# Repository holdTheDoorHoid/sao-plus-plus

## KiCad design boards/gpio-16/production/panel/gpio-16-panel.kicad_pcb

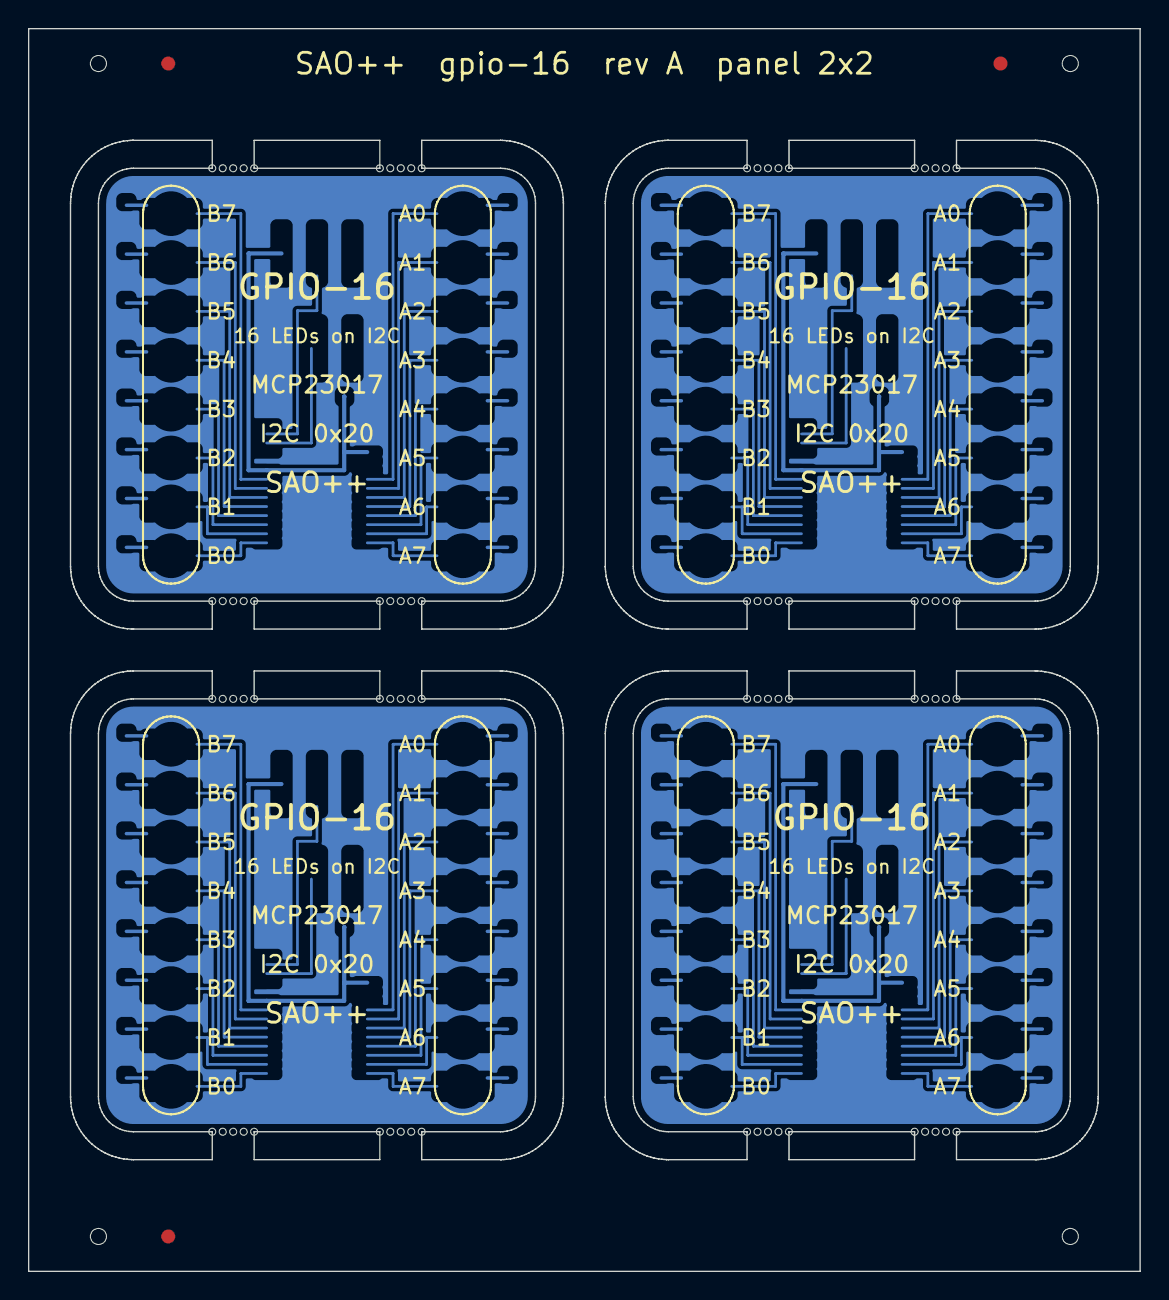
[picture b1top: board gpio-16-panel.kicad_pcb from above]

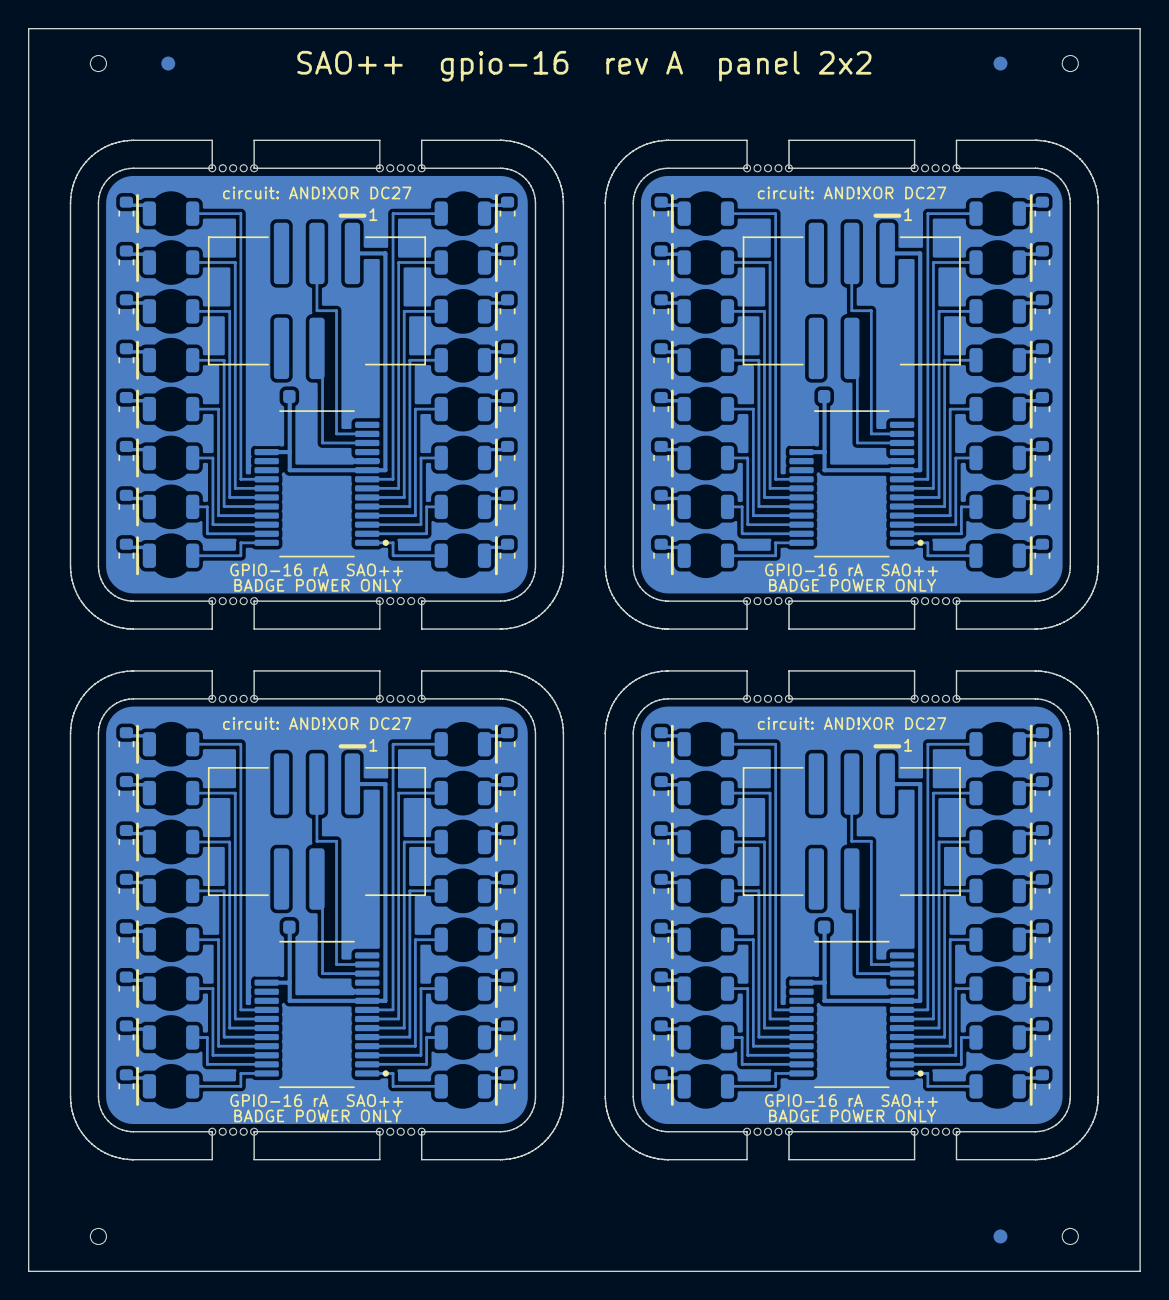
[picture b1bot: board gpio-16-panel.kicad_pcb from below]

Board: 2 copper layers, 79.6 x 89.0 mm, 140 parts (140 on the bottom side), 144 nets.

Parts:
C101, C201, C301, C401: 100n; SAOPP_C_0603_1608Metric
D101, D102, D103, D104, D105, D106, D107, D108, D109, D110, D111, D112, D113, D114, D115, D116, D201, D202, D203, D204, D205, D206, D207, D208, D209, D210, D211, D212, D213, D214, D215, D216, D301, D302, D303, D304, D305, D306, D307, D308, D309, D310, D311, D312, D313, D314, D315, D316, D401, D402, D403, D404, D405, D406, D407, D408, D409, D410, D411, D412, D413, D414, D415, D416: red; SAOPP_LED-10_1206_ReverseMount_ThroughBoard
J101, J201, J301, J401: SAO v1.69bis; SAOPP_CONN-01_BoxHeader_2x03_P2.54mm_SMD_XFCN_BH254VS-6P
R101, R102, R103, R104, R105, R106, R107, R108, R109, R110, R111, R112, R113, R114, R115, R116, R201, R202, R203, R204, R205, R206, R207, R208, R209, R210, R211, R212, R213, R214, R215, R216, R301, R302, R303, R304, R305, R306, R307, R308, R309, R310, R311, R312, R313, R314, R315, R316, R401, R402, R403, R404, R405, R406, R407, R408, R409, R410, R411, R412, R413, R414, R415, R416: 1.3k; SAOPP_R_0603_1608Metric
U101, U201, U301, U401: MCP23017; SSOP-28_5.3x10.2mm_P0.65mm_Microchip_C04-2073A

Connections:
B2-D1_K: D201.1, R201.1
B2-D2_K: D202.1, R202.1
B2-D3_K: D203.1, R203.1
B2-D4_K: D204.1, R204.1
B2-D5_K: D205.1, R205.1
B2-D6_K: D206.1, R206.1
B2-D7_K: D207.1, R207.1
B2-D8_K: D208.1, R208.1
B2-D9_K: D209.1, R209.1
B2-D10_K: D210.1, R210.1
B2-D11_K: D211.1, R211.1
B2-D12_K: D212.1, R212.1
B2-D13_K: D213.1, R213.1
B2-D14_K: D214.1, R214.1
B2-D15_K: D215.1, R215.1
B2-D16_K: D216.1, R216.1
B2-GND: C201.2, J201.2, R201.2, R202.2, R203.2, R204.2, R205.2, R206.2, R207.2, R208.2, R209.2, R210.2, R211.2, R212.2, R213.2, R214.2, R215.2, R216.2, U201.10, U201.15, U201.16, U201.17
B2-GPA0: D201.2, U201.21
B2-GPA1: D202.2, U201.22
B2-GPA2: D203.2, U201.23
B2-GPA3: D204.2, U201.24
B2-GPA4: D205.2, U201.25
B2-GPA5: D206.2, U201.26
B2-GPA6: D207.2, U201.27
B2-GPA7: D208.2, U201.28
B2-GPB0: D209.2, U201.1
B2-GPB1: D210.2, U201.2
B2-GPB2: D211.2, U201.3
B2-GPB3: D212.2, U201.4
B2-GPB4: D213.2, U201.5
B2-GPB5: D214.2, U201.6
B2-GPB6: D215.2, U201.7
B2-GPB7: D216.2, U201.8
B2-SCL: J201.4, U201.12
B2-SDA: J201.3, U201.13
B2-VSAO: C201.1, J201.1, U201.9, U201.18
B3-D1_K: D301.1, R301.1
B3-D2_K: D302.1, R302.1
B3-D3_K: D303.1, R303.1
B3-D4_K: D304.1, R304.1
B3-D5_K: D305.1, R305.1
B3-D6_K: D306.1, R306.1
B3-D7_K: D307.1, R307.1
B3-D8_K: D308.1, R308.1
B3-D9_K: D309.1, R309.1
B3-D10_K: D310.1, R310.1
B3-D11_K: D311.1, R311.1
B3-D12_K: D312.1, R312.1
B3-D13_K: D313.1, R313.1
B3-D14_K: D314.1, R314.1
B3-D15_K: D315.1, R315.1
B3-D16_K: D316.1, R316.1
B3-GND: C301.2, J301.2, R301.2, R302.2, R303.2, R304.2, R305.2, R306.2, R307.2, R308.2, R309.2, R310.2, R311.2, R312.2, R313.2, R314.2, R315.2, R316.2, U301.10, U301.15, U301.16, U301.17
B3-GPA0: D301.2, U301.21
B3-GPA1: D302.2, U301.22
B3-GPA2: D303.2, U301.23
B3-GPA3: D304.2, U301.24
B3-GPA4: D305.2, U301.25
B3-GPA5: D306.2, U301.26
B3-GPA6: D307.2, U301.27
B3-GPA7: D308.2, U301.28
B3-GPB0: D309.2, U301.1
B3-GPB1: D310.2, U301.2
B3-GPB2: D311.2, U301.3
B3-GPB3: D312.2, U301.4
B3-GPB4: D313.2, U301.5
B3-GPB5: D314.2, U301.6
B3-GPB6: D315.2, U301.7
B3-GPB7: D316.2, U301.8
B3-SCL: J301.4, U301.12
B3-SDA: J301.3, U301.13
B3-VSAO: C301.1, J301.1, U301.9, U301.18
B4-D1_K: D401.1, R401.1
B4-D2_K: D402.1, R402.1
B4-D3_K: D403.1, R403.1
B4-D4_K: D404.1, R404.1
B4-D5_K: D405.1, R405.1
B4-D6_K: D406.1, R406.1
B4-D7_K: D407.1, R407.1
B4-D8_K: D408.1, R408.1
B4-D9_K: D409.1, R409.1
B4-D10_K: D410.1, R410.1
B4-D11_K: D411.1, R411.1
B4-D12_K: D412.1, R412.1
B4-D13_K: D413.1, R413.1
B4-D14_K: D414.1, R414.1
B4-D15_K: D415.1, R415.1
B4-D16_K: D416.1, R416.1
B4-GND: C401.2, J401.2, R401.2, R402.2, R403.2, R404.2, R405.2, R406.2, R407.2, R408.2, R409.2, R410.2, R411.2, R412.2, R413.2, R414.2, R415.2, R416.2, U401.10, U401.15, U401.16, U401.17
B4-GPA0: D401.2, U401.21
B4-GPA1: D402.2, U401.22
B4-GPA2: D403.2, U401.23
B4-GPA3: D404.2, U401.24
B4-GPA4: D405.2, U401.25
B4-GPA5: D406.2, U401.26
B4-GPA6: D407.2, U401.27
B4-GPA7: D408.2, U401.28
B4-GPB0: D409.2, U401.1
B4-GPB1: D410.2, U401.2
B4-GPB2: D411.2, U401.3
B4-GPB3: D412.2, U401.4
B4-GPB4: D413.2, U401.5
B4-GPB5: D414.2, U401.6
B4-GPB6: D415.2, U401.7
B4-GPB7: D416.2, U401.8
B4-SCL: J401.4, U401.12
B4-SDA: J401.3, U401.13
B4-VSAO: C401.1, J401.1, U401.9, U401.18
D1_K: D101.1, R101.1
D2_K: D102.1, R102.1
D3_K: D103.1, R103.1
D4_K: D104.1, R104.1
D5_K: D105.1, R105.1
D6_K: D106.1, R106.1
D7_K: D107.1, R107.1
D8_K: D108.1, R108.1
D9_K: D109.1, R109.1
D10_K: D110.1, R110.1
D11_K: D111.1, R111.1
D12_K: D112.1, R112.1
D13_K: D113.1, R113.1
D14_K: D114.1, R114.1
D15_K: D115.1, R115.1
D16_K: D116.1, R116.1
GND: C101.2, J101.2, R101.2, R102.2, R103.2, R104.2, R105.2, R106.2, R107.2, R108.2, R109.2, R110.2, R111.2, R112.2, R113.2, R114.2, R115.2, R116.2, U101.10, U101.15, U101.16, U101.17
GPA0: D101.2, U101.21
GPA1: D102.2, U101.22
GPA2: D103.2, U101.23
GPA3: D104.2, U101.24
GPA4: D105.2, U101.25
GPA5: D106.2, U101.26
GPA6: D107.2, U101.27
GPA7: D108.2, U101.28
GPB0: D109.2, U101.1
GPB1: D110.2, U101.2
GPB2: D111.2, U101.3
GPB3: D112.2, U101.4
GPB4: D113.2, U101.5
GPB5: D114.2, U101.6
GPB6: D115.2, U101.7
GPB7: D116.2, U101.8
SCL: J101.4, U101.12
SDA: J101.3, U101.13
VSAO: C101.1, J101.1, U101.9, U101.18

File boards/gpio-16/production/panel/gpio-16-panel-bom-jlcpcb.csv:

Comment,Designator,Footprint,LCSC Part #
100n,"C101,C201,C301,C401",SAOPP_C_0603_1608Metric,C14663
red,"D101,D102,D103,D104,D105,D106,D107,D108,D109,D110,D111,D112,D113,D114,D115,D116,D201,D202,D203,D204,D205,D206,D207,D208,D209,D210,D211,D212,D213,D214,D215,D216,D301,D302,D303,D304,D305,D306,D307,D308,D309,D310,D311,D312,D313,D314,D315,D316,D401,D402,D403,D404,D405,D406,D407,D408,D409,D410,D411,D412,D413,D414,D415,D416",SAOPP_LED-10_1206_ReverseMount_ThroughBoard,C125107
SAO v1.69bis,"J101,J201,J301,J401",SAOPP_CONN-01_BoxHeader_2x03_P2.54mm_SMD_XFCN_BH254VS-6P,C492445
1.3k,"R101,R102,R103,R104,R105,R106,R107,R108,R109,R110,R111,R112,R113,R114,R115,R116,R201,R202,R203,R204,R205,R206,R207,R208,R209,R210,R211,R212,R213,R214,R215,R216,R301,R302,R303,R304,R305,R306,R307,R308,R309,R310,R311,R312,R313,R314,R315,R316,R401,R402,R403,R404,R405,R406,R407,R408,R409,R410,R411,R412,R413,R414,R415,R416",SAOPP_R_0603_1608Metric,C22767
MCP23017,"U101,U201,U301,U401",SSOP-28_5.3x10.2mm_P0.65mm_Microchip_C04-2073A,C558584

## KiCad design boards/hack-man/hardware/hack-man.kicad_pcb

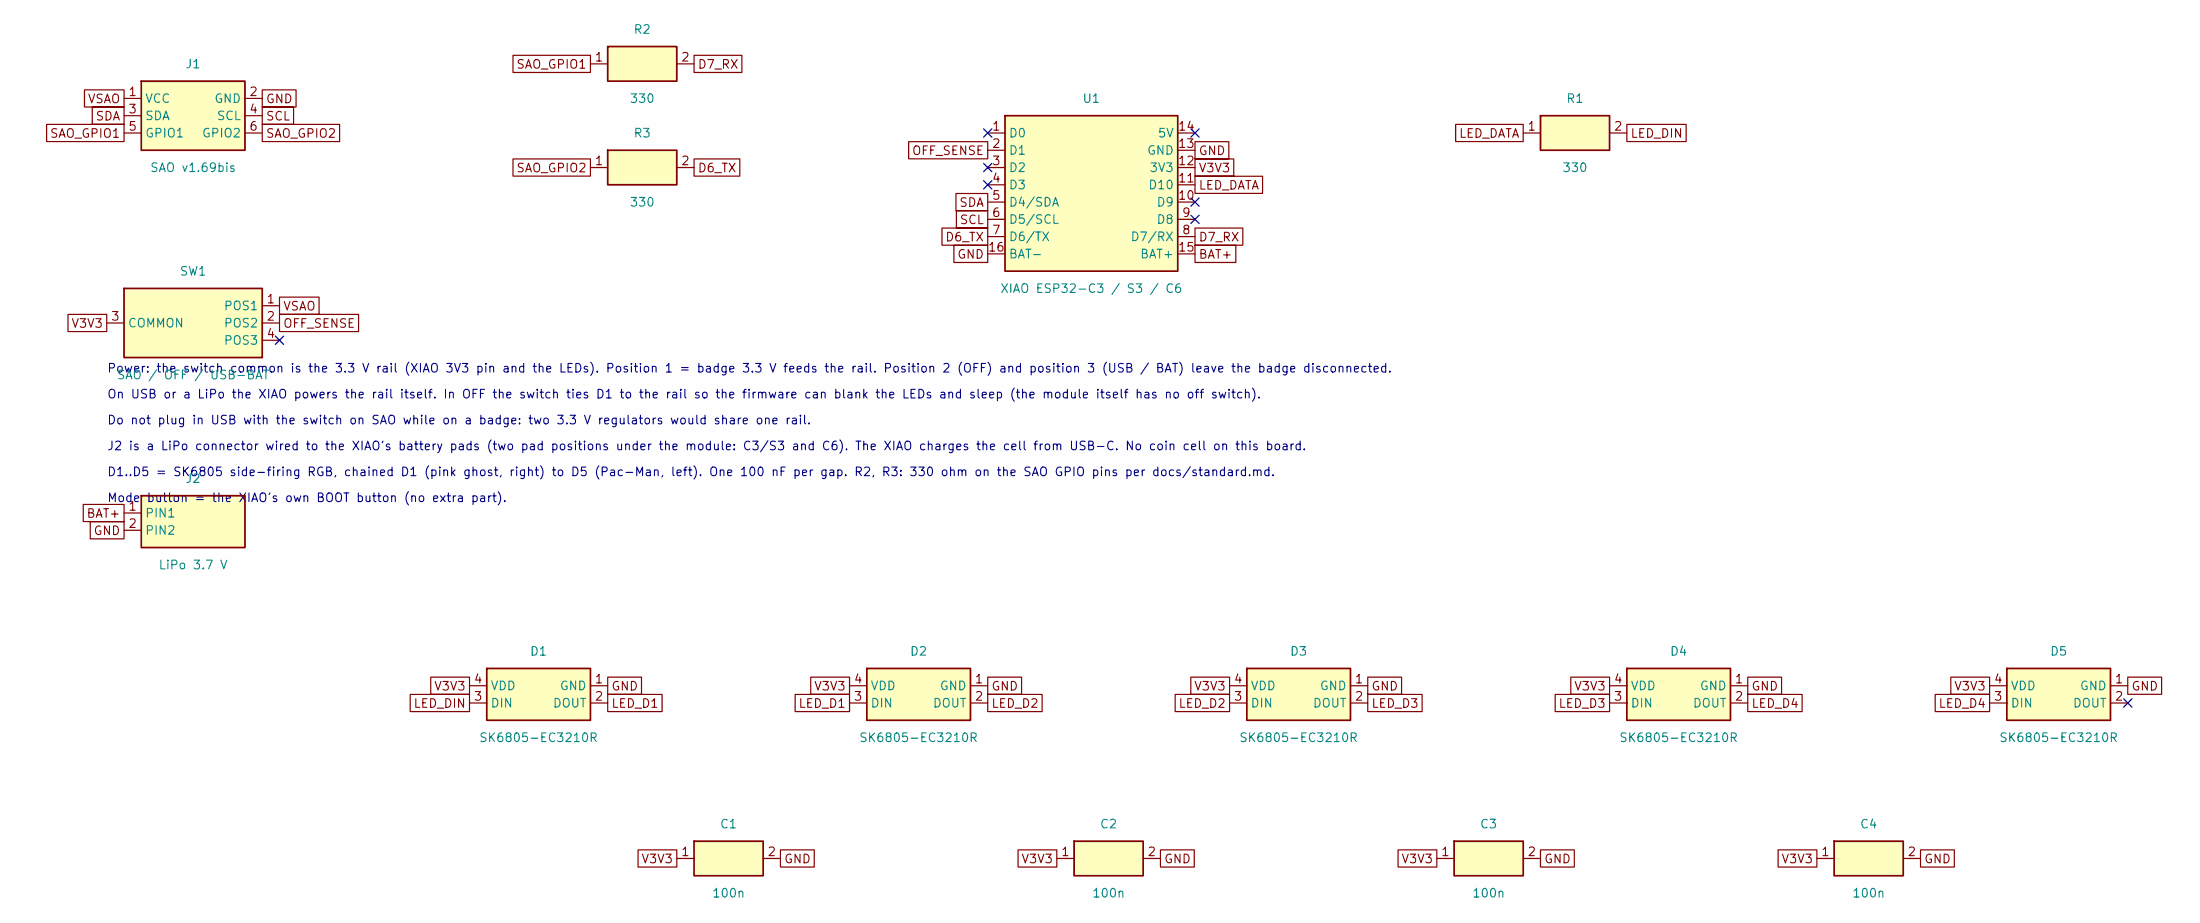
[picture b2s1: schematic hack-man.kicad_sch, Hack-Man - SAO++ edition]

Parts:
C1, C2, C3, C4: 100n; SAOPP_C_0603_1608Metric; MPN CC0603KRX7R9BB104; LCSC C14663
D1, D2, D3, D4, D5: SK6805-EC3210R; SAOPP_LED-20_SK6805-EC3210R_SideView_RGB; MPN SK6805-EC3210R; LCSC C5378735
J1: SAO v1.69bis; SAOPP_CONN-01_BoxHeader_2x03_P2.54mm_SMD_XFCN_BH254VS-6P; MPN BH254VS-6P; LCSC C492445
J2: LiPo 3.7 V; SAOPP_CONN-10_JST_PH_S2B-PH-SM4-TB_1x02_Horizontal; MPN S2B-PH-SM4-TB(LF)(SN); LCSC C295747
R1, R2, R3: 330; SAOPP_R_0603_1608Metric; MPN 0603WAF3300T5E; LCSC C23138
SW1: SAO / OFF / USB-BAT; SAOPP_SW-01_Slide_SP3T_CK_PCM13SMTR; MPN PCM13SMTR; LCSC C221842
U1: XIAO ESP32-C3 / S3 / C6; SAOPP_MCU-01_Seeed_XIAO_SMD_C3_S3_C6; MPN XIAO ESP32-C3 / S3 / C6

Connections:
BAT+: J2.1 (PIN1), U1.15 (BAT+)
D6_TX: R3.2, U1.7 (D6/TX)
D7_RX: R2.2, U1.8 (D7/RX)
GND: C1.2, C2.2, C3.2, C4.2, D1.1 (GND), D2.1 (GND), D3.1 (GND), D4.1 (GND), D5.1 (GND), J1.2 (GND), J2.2 (PIN2), U1.13 (GND), U1.16 (BAT-)
LED_D1: D1.2 (DOUT), D2.3 (DIN)
LED_D2: D2.2 (DOUT), D3.3 (DIN)
LED_D3: D3.2 (DOUT), D4.3 (DIN)
LED_D4: D4.2 (DOUT), D5.3 (DIN)
LED_DATA: R1.1, U1.11 (D10)
LED_DIN: D1.3 (DIN), R1.2
OFF_SENSE: SW1.2 (POS2), U1.2 (D1)
SAO_GPIO1: J1.5 (GPIO1), R2.1
SAO_GPIO2: J1.6 (GPIO2), R3.1
SCL: J1.4 (SCL), U1.6 (D5/SCL)
SDA: J1.3 (SDA), U1.5 (D4/SDA)
V3V3: C1.1, C2.1, C3.1, C4.1, D1.4 (VDD), D2.4 (VDD), D3.4 (VDD), D4.4 (VDD), D5.4 (VDD), SW1.3 (COMMON), U1.12 (3V3)
VSAO: J1.1 (VCC), SW1.1 (POS1)

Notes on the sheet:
Power: the switch common is the 3.3 V rail (XIAO 3V3 pin and the LEDs). Position 1 = badge 3.3 V feeds the rail. Position 2 (OFF) and position 3 (USB / BAT) leave the badge disconnected.
On USB or a LiPo the XIAO powers the rail itself. In OFF the switch ties D1 to the rail so the firmware can blank the LEDs and sleep (the module itself has no off switch).
Do not plug in USB with the switch on SAO while on a badge: two 3.3 V regulators would share one rail.
J2 is a LiPo connector wired to the XIAO's battery pads (two pad positions under the module: C3/S3 and C6). The XIAO charges the cell from USB-C. No coin cell on this board.
D1..D5 = SK6805 side-firing RGB, chained D1 (pink ghost, right) to D5 (Pac-Man, left). One 100 nF per gap. R2, R3: 330 ohm on the SAO GPIO pins per docs/standard.md.
Mode button = the XIAO's own BOOT button (no extra part).

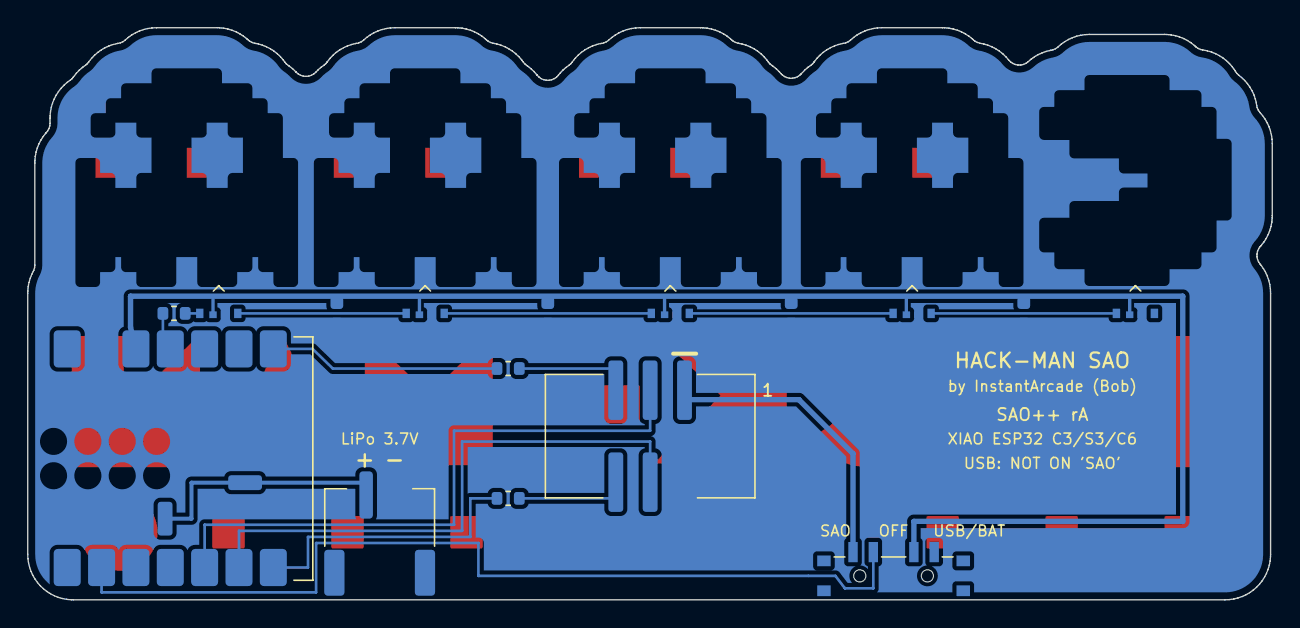
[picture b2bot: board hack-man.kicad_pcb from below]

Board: 2 copper layers, 92.0 x 42.3 mm, 16 parts (16 on the bottom side), 17 nets.

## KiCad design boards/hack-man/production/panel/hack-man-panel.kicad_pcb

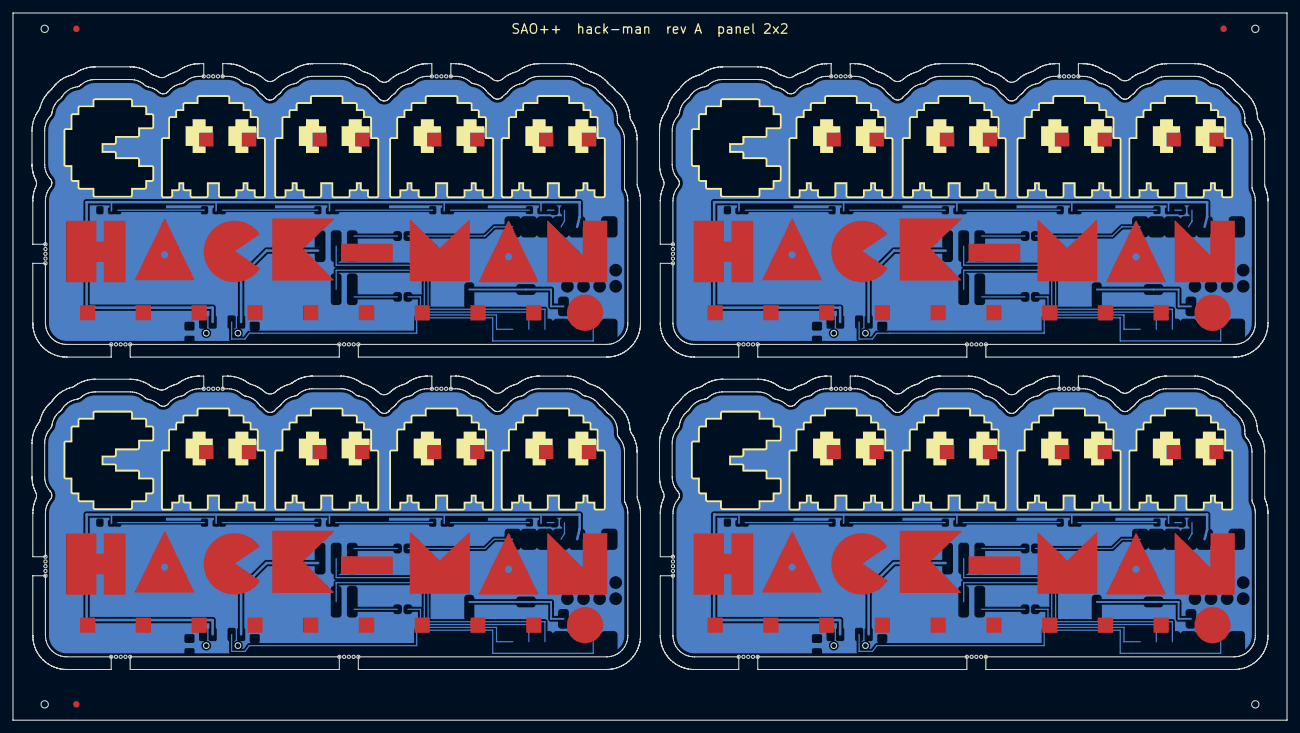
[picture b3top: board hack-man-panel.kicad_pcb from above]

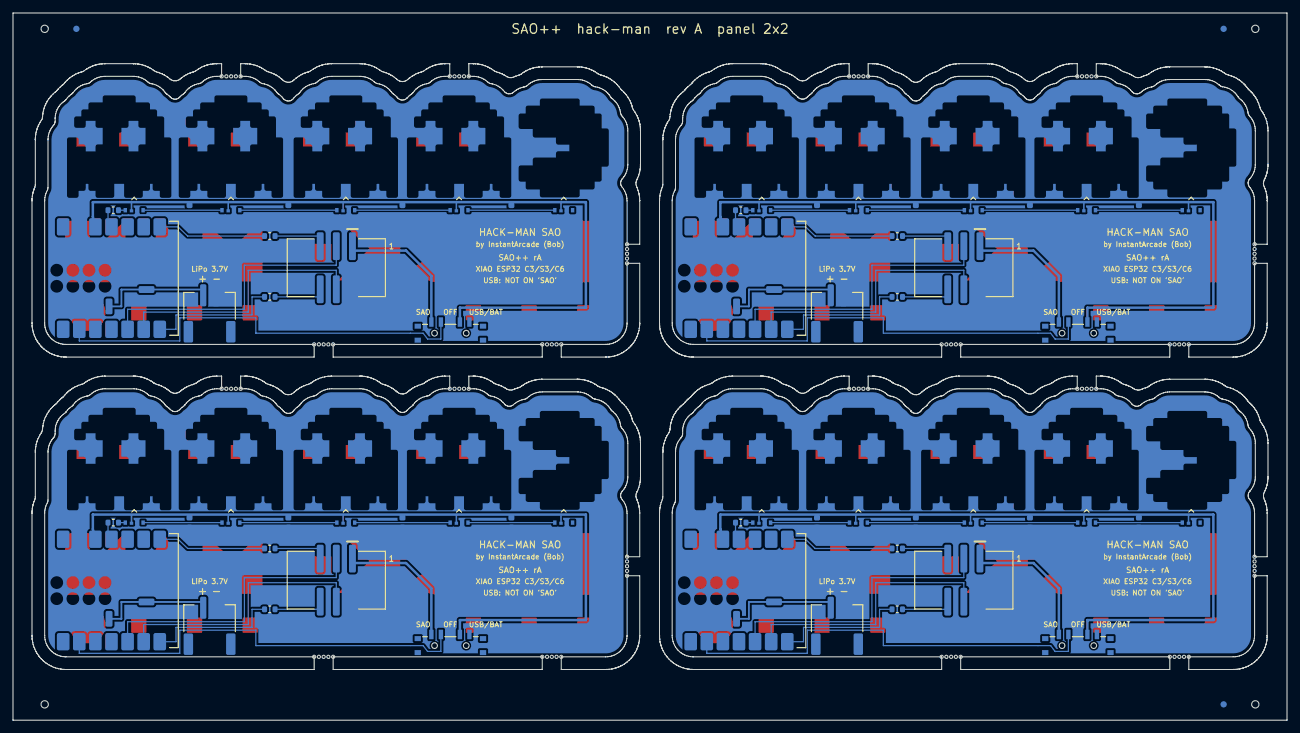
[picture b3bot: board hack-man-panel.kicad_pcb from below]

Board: 2 copper layers, 201.0 x 111.6 mm, 64 parts (64 on the bottom side), 68 nets.

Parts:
C101, C102, C103, C104, C201, C202, C203, C204, C301, C302, C303, C304, C401, C402, C403, C404: 100n; SAOPP_C_0603_1608Metric
D101, D102, D103, D104, D105, D201, D202, D203, D204, D205, D301, D302, D303, D304, D305, D401, D402, D403, D404, D405: SK6805-EC3210R; SAOPP_LED-20_SK6805-EC3210R_SideView_RGB
J101, J201, J301, J401: SAO v1.69bis; SAOPP_CONN-01_BoxHeader_2x03_P2.54mm_SMD_XFCN_BH254VS-6P
J102, J202, J302, J402: LiPo 3.7 V; SAOPP_CONN-10_JST_PH_S2B-PH-SM4-TB_1x02_Horizontal
R101, R102, R103, R201, R202, R203, R301, R302, R303, R401, R402, R403: 330; SAOPP_R_0603_1608Metric
SW101, SW201, SW301, SW401: SAO / OFF / USB-BAT; SAOPP_SW-01_Slide_SP3T_CK_PCM13SMTR
U101, U201, U301, U401: XIAO ESP32-C3 / S3 / C6; SAOPP_MCU-01_Seeed_XIAO_SMD_C3_S3_C6

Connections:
B2-BAT+: J202.1, U201.15
B2-D6_TX: R203.2, U201.7
B2-D7_RX: R202.2, U201.8
B2-GND: C201.2, C202.2, C203.2, C204.2, D201.1, D202.1, D203.1, D204.1, D205.1, J201.2, J202.2, U201.13, U201.16
B2-LED_D1: D201.2, D202.3
B2-LED_D2: D202.2, D203.3
B2-LED_D3: D203.2, D204.3
B2-LED_D4: D204.2, D205.3
B2-LED_DATA: R201.1, U201.11
B2-LED_DIN: D201.3, R201.2
B2-OFF_SENSE: SW201.2, U201.2
B2-SAO_GPIO1: J201.5, R202.1
B2-SAO_GPIO2: J201.6, R203.1
B2-SCL: J201.4, U201.6
B2-SDA: J201.3, U201.5
B2-V3V3: C201.1, C202.1, C203.1, C204.1, D201.4, D202.4, D203.4, D204.4, D205.4, SW201.3, U201.12
B2-VSAO: J201.1, SW201.1
B3-BAT+: J302.1, U301.15
B3-D6_TX: R303.2, U301.7
B3-D7_RX: R302.2, U301.8
B3-GND: C301.2, C302.2, C303.2, C304.2, D301.1, D302.1, D303.1, D304.1, D305.1, J301.2, J302.2, U301.13, U301.16
B3-LED_D1: D301.2, D302.3
B3-LED_D2: D302.2, D303.3
B3-LED_D3: D303.2, D304.3
B3-LED_D4: D304.2, D305.3
B3-LED_DATA: R301.1, U301.11
B3-LED_DIN: D301.3, R301.2
B3-OFF_SENSE: SW301.2, U301.2
B3-SAO_GPIO1: J301.5, R302.1
B3-SAO_GPIO2: J301.6, R303.1
B3-SCL: J301.4, U301.6
B3-SDA: J301.3, U301.5
B3-V3V3: C301.1, C302.1, C303.1, C304.1, D301.4, D302.4, D303.4, D304.4, D305.4, SW301.3, U301.12
B3-VSAO: J301.1, SW301.1
B4-BAT+: J402.1, U401.15
B4-D6_TX: R403.2, U401.7
B4-D7_RX: R402.2, U401.8
B4-GND: C401.2, C402.2, C403.2, C404.2, D401.1, D402.1, D403.1, D404.1, D405.1, J401.2, J402.2, U401.13, U401.16
B4-LED_D1: D401.2, D402.3
B4-LED_D2: D402.2, D403.3
B4-LED_D3: D403.2, D404.3
B4-LED_D4: D404.2, D405.3
B4-LED_DATA: R401.1, U401.11
B4-LED_DIN: D401.3, R401.2
B4-OFF_SENSE: SW401.2, U401.2
B4-SAO_GPIO1: J401.5, R402.1
B4-SAO_GPIO2: J401.6, R403.1
B4-SCL: J401.4, U401.6
B4-SDA: J401.3, U401.5
B4-V3V3: C401.1, C402.1, C403.1, C404.1, D401.4, D402.4, D403.4, D404.4, D405.4, SW401.3, U401.12
B4-VSAO: J401.1, SW401.1
BAT+: J102.1, U101.15
D6_TX: R103.2, U101.7
D7_RX: R102.2, U101.8
GND: C101.2, C102.2, C103.2, C104.2, D101.1, D102.1, D103.1, D104.1, D105.1, J101.2, J102.2, U101.13, U101.16
LED_D1: D101.2, D102.3
LED_D2: D102.2, D103.3
LED_D3: D103.2, D104.3
LED_D4: D104.2, D105.3
LED_DATA: R101.1, U101.11
LED_DIN: D101.3, R101.2
OFF_SENSE: SW101.2, U101.2
SAO_GPIO1: J101.5, R102.1
SAO_GPIO2: J101.6, R103.1
SCL: J101.4, U101.6
SDA: J101.3, U101.5
V3V3: C101.1, C102.1, C103.1, C104.1, D101.4, D102.4, D103.4, D104.4, D105.4, SW101.3, U101.12
VSAO: J101.1, SW101.1

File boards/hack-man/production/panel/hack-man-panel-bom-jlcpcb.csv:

Comment,Designator,Footprint,LCSC Part #
100n,"C101,C102,C103,C104,C201,C202,C203,C204,C301,C302,C303,C304,C401,C402,C403,C404",SAOPP_C_0603_1608Metric,C14663
SK6805-EC3210R,"D101,D102,D103,D104,D105,D201,D202,D203,D204,D205,D301,D302,D303,D304,D305,D401,D402,D403,D404,D405",SAOPP_LED-20_SK6805-EC3210R_SideView_RGB,C5378735
SAO v1.69bis,"J101,J201,J301,J401",SAOPP_CONN-01_BoxHeader_2x03_P2.54mm_SMD_XFCN_BH254VS-6P,C492445
LiPo 3.7 V,"J102,J202,J302,J402",SAOPP_CONN-10_JST_PH_S2B-PH-SM4-TB_1x02_Horizontal,C295747
330,"R101,R102,R103,R201,R202,R203,R301,R302,R303,R401,R402,R403",SAOPP_R_0603_1608Metric,C23138
SAO / OFF / USB-BAT,"SW101,SW201,SW301,SW401",SAOPP_SW-01_Slide_SP3T_CK_PCM13SMTR,C221842
XIAO ESP32-C3 / S3 / C6,"U101,U201,U301,U401",SAOPP_MCU-01_Seeed_XIAO_SMD_C3_S3_C6,

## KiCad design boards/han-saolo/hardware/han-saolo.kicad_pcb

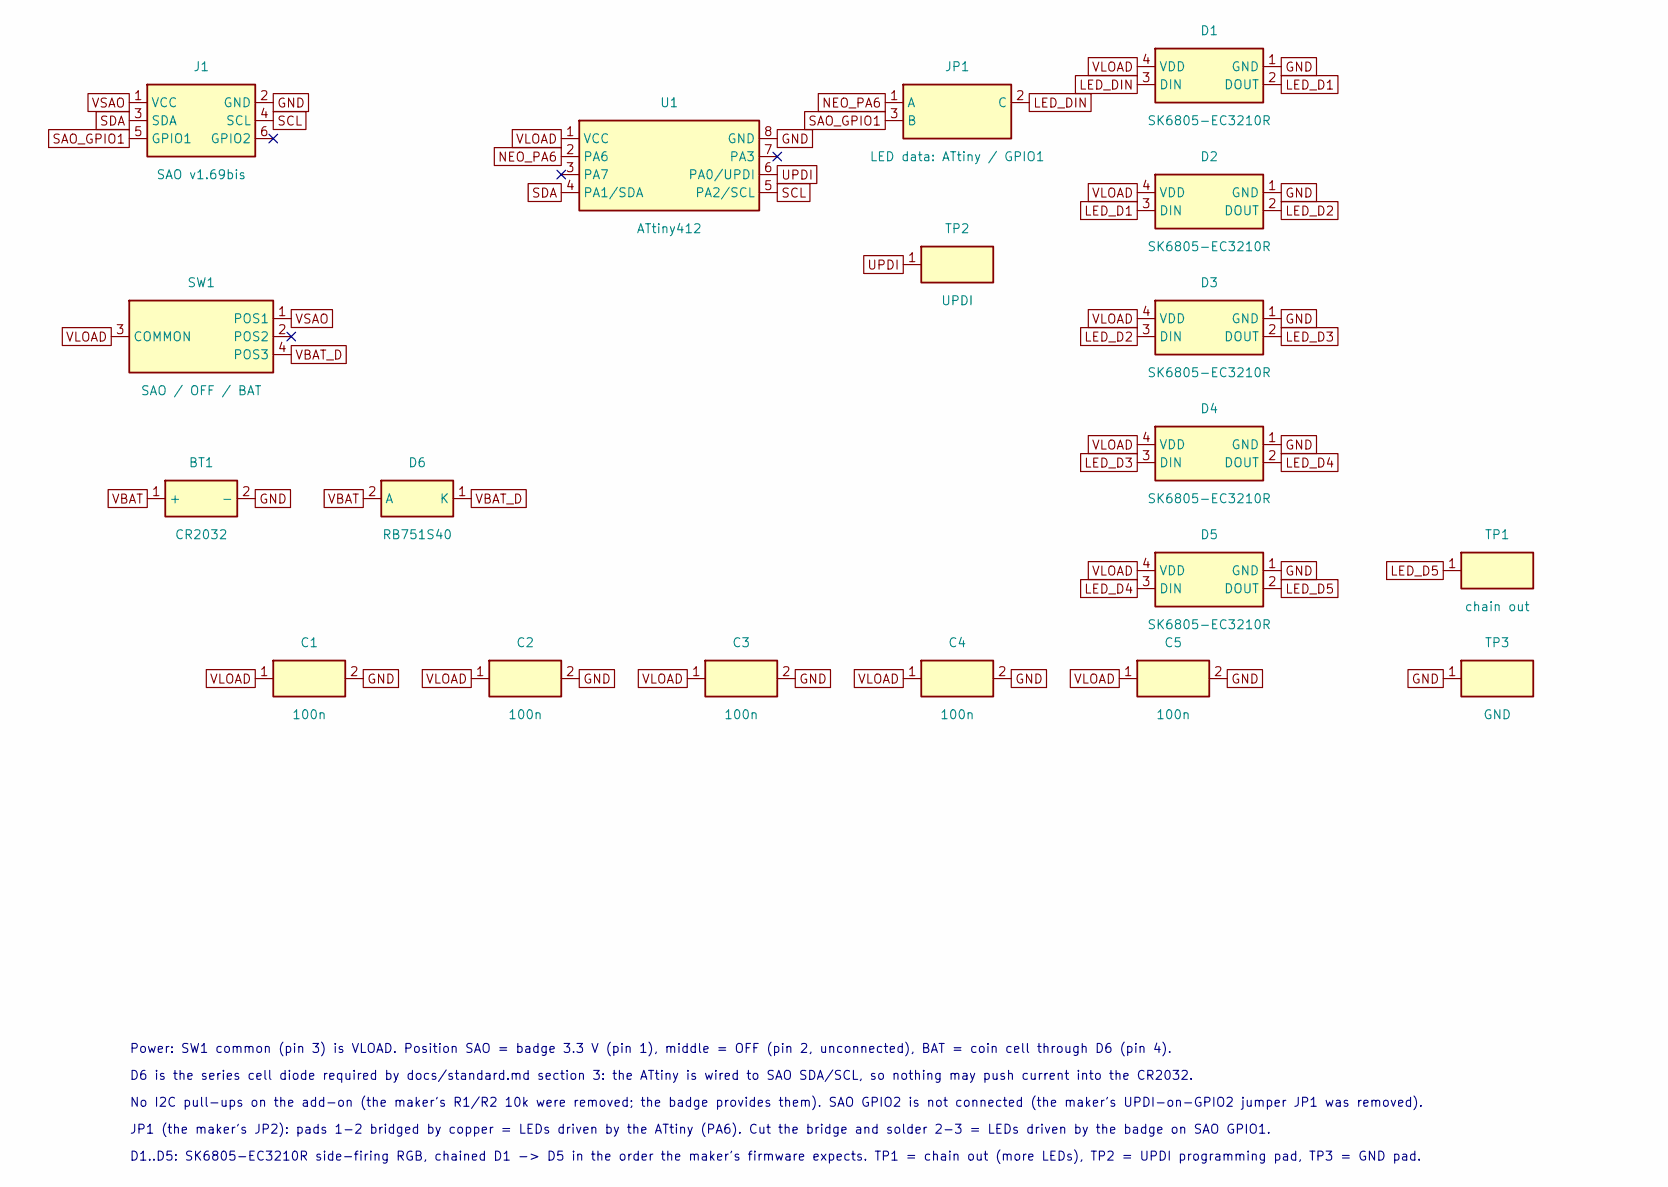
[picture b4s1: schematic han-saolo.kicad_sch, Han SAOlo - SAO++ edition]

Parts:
BT1: CR2032; SAOPP_BAT-01_CR2032_SMD_TE_BAT-HLD-001; MPN BAT-HLD-001; LCSC C7501066
C1, C2, C3, C4, C5: 100n; SAOPP_C_0603_1608Metric; MPN CC0603KRX7R9BB104; LCSC C14663
D1, D2, D3, D4, D5: SK6805-EC3210R; SAOPP_LED-20_SK6805-EC3210R_SideView_RGB; MPN SK6805-EC3210R; LCSC C5378735
D6: RB751S40; D_SOD-523; MPN RB751S40T1G; LCSC C232576
J1: SAO v1.69bis; SAOPP_CONN-01_BoxHeader_2x03_P2.54mm_SMD_XFCN_BH254VS-6P; MPN BH254VS-6P; LCSC C492445
JP1: LED data: ATtiny / GPIO1; SolderJumper-3_P1.3mm_Bridged2Bar12_RoundedPad1.0x1.5mm; MPN none: PCB copper, nothing fitted
SW1: SAO / OFF / BAT; SAOPP_SW-01_Slide_SP3T_CK_PCM13SMTR; MPN PCM13SMTR; LCSC C221842
TP1: chain out; TestPoint_Pad_D2.0mm; MPN none: bare pad, nothing fitted
TP2: UPDI; TestPoint_Pad_D1.5mm; MPN none: bare pad, nothing fitted
TP3: GND; TestPoint_Pad_D3.0mm; MPN none: bare pad, nothing fitted
U1: ATtiny412; SOIC-8_3.9x4.9mm_P1.27mm; MPN ATTINY412-SSNR; LCSC C1337190

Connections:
GND: BT1.2 (-), C1.2, C2.2, C3.2, C4.2, C5.2, D1.1 (GND), D2.1 (GND), D3.1 (GND), D4.1 (GND), D5.1 (GND), J1.2 (GND), TP3.1, U1.8 (GND)
LED_D1: D1.2 (DOUT), D2.3 (DIN)
LED_D2: D2.2 (DOUT), D3.3 (DIN)
LED_D3: D3.2 (DOUT), D4.3 (DIN)
LED_D4: D4.2 (DOUT), D5.3 (DIN)
LED_D5: D5.2 (DOUT), TP1.1
LED_DIN: D1.3 (DIN), JP1.2 (C)
NEO_PA6: JP1.1 (A), U1.2 (PA6)
SAO_GPIO1: J1.5 (GPIO1), JP1.3 (B)
SCL: J1.4 (SCL), U1.5 (PA2/SCL)
SDA: J1.3 (SDA), U1.4 (PA1/SDA)
UPDI: TP2.1, U1.6 (PA0/UPDI)
VBAT: BT1.1 (+), D6.2 (A)
VBAT_D: D6.1 (K), SW1.4 (POS3)
VLOAD: C1.1, C2.1, C3.1, C4.1, C5.1, D1.4 (VDD), D2.4 (VDD), D3.4 (VDD), D4.4 (VDD), D5.4 (VDD), SW1.3 (COMMON), U1.1 (VCC)
VSAO: J1.1 (VCC), SW1.1 (POS1)

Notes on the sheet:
Power: SW1 common (pin 3) is VLOAD. Position SAO = badge 3.3 V (pin 1), middle = OFF (pin 2, unconnected), BAT = coin cell through D6 (pin 4).
D6 is the series cell diode required by docs/standard.md section 3: the ATtiny is wired to SAO SDA/SCL, so nothing may push current into the CR2032.
No I2C pull-ups on the add-on (the maker's R1/R2 10k were removed; the badge provides them). SAO GPIO2 is not connected (the maker's UPDI-on-GPIO2 jumper JP1 was removed).
JP1 (the maker's JP2): pads 1-2 bridged by copper = LEDs driven by the ATtiny (PA6). Cut the bridge and solder 2-3 = LEDs driven by the badge on SAO GPIO1.
D1..D5: SK6805-EC3210R side-firing RGB, chained D1 -> D5 in the order the maker's firmware expects. TP1 = chain out (more LEDs), TP2 = UPDI programming pad, TP3 = GND pad.

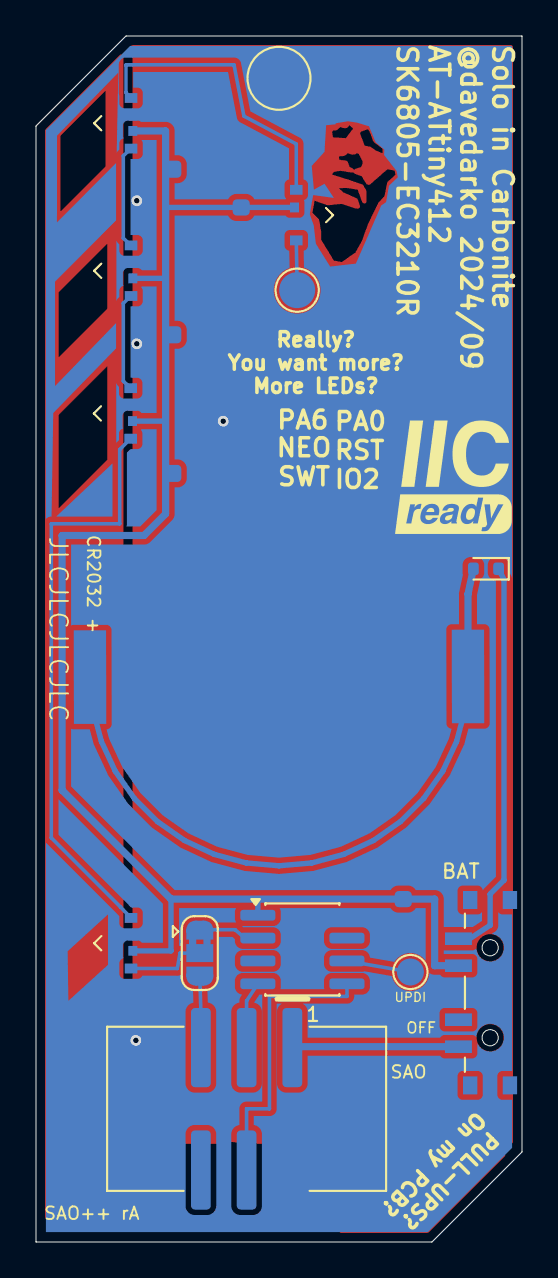
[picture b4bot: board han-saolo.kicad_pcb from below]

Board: 2 copper layers, 27.0 x 67.0 mm, 19 parts (19 on the bottom side), 16 nets.

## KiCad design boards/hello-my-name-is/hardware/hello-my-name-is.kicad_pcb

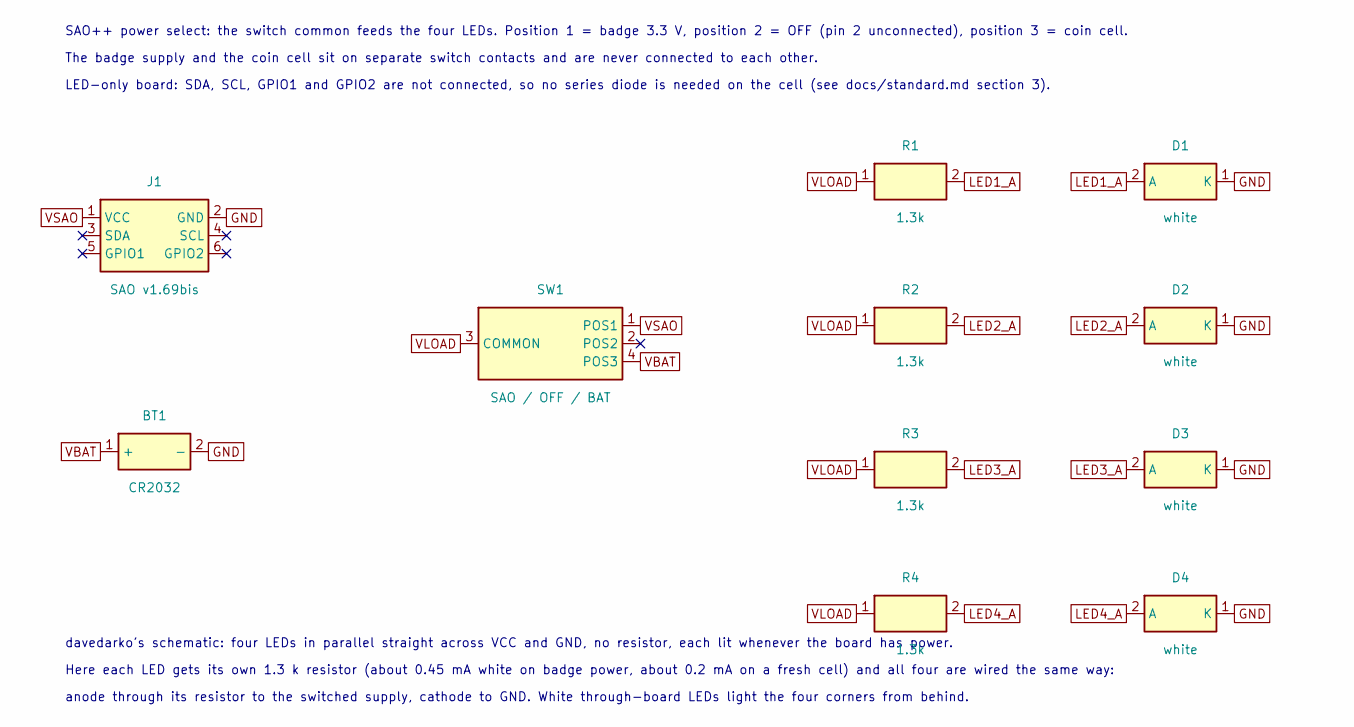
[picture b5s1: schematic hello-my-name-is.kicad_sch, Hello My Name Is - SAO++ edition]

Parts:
BT1: CR2032; SAOPP_BAT-01_CR2032_SMD_TE_BAT-HLD-001; MPN BAT-HLD-001; LCSC C7501066
D1, D2, D3, D4: white; SAOPP_LED-10_1206_ReverseMount_ThroughBoard; MPN LTW-C230DS; LCSC C575513
J1: SAO v1.69bis; SAOPP_CONN-01_BoxHeader_2x03_P2.54mm_SMD_XFCN_BH254VS-6P; MPN BH254VS-6P; LCSC C492445
R1, R2, R3, R4: 1.3k; SAOPP_R_0603_1608Metric; MPN 0603WAF1301T5E; LCSC C22767
SW1: SAO / OFF / BAT; SAOPP_SW-01_Slide_SP3T_CK_PCM13SMTR; MPN PCM13SMTR; LCSC C221842

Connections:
GND: BT1.2 (-), D1.1 (K), D2.1 (K), D3.1 (K), D4.1 (K), J1.2 (GND)
LED1_A: D1.2 (A), R1.2
LED2_A: D2.2 (A), R2.2
LED3_A: D3.2 (A), R3.2
LED4_A: D4.2 (A), R4.2
VBAT: BT1.1 (+), SW1.4 (POS3)
VLOAD: R1.1, R2.1, R3.1, R4.1, SW1.3 (COMMON)
VSAO: J1.1 (VCC), SW1.1 (POS1)

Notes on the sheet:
SAO++ power select: the switch common feeds the four LEDs. Position 1 = badge 3.3 V, position 2 = OFF (pin 2 unconnected), position 3 = coin cell.
The badge supply and the coin cell sit on separate switch contacts and are never connected to each other.
LED-only board: SDA, SCL, GPIO1 and GPIO2 are not connected, so no series diode is needed on the cell (see docs/standard.md section 3).
davedarko's schematic: four LEDs in parallel straight across VCC and GND, no resistor, each lit whenever the board has power.
Here each LED gets its own 1.3 k resistor (about 0.45 mA white on badge power, about 0.2 mA on a fresh cell) and all four are wired the same way:
anode through its resistor to the switched supply, cathode to GND. White through-board LEDs light the four corners from behind.

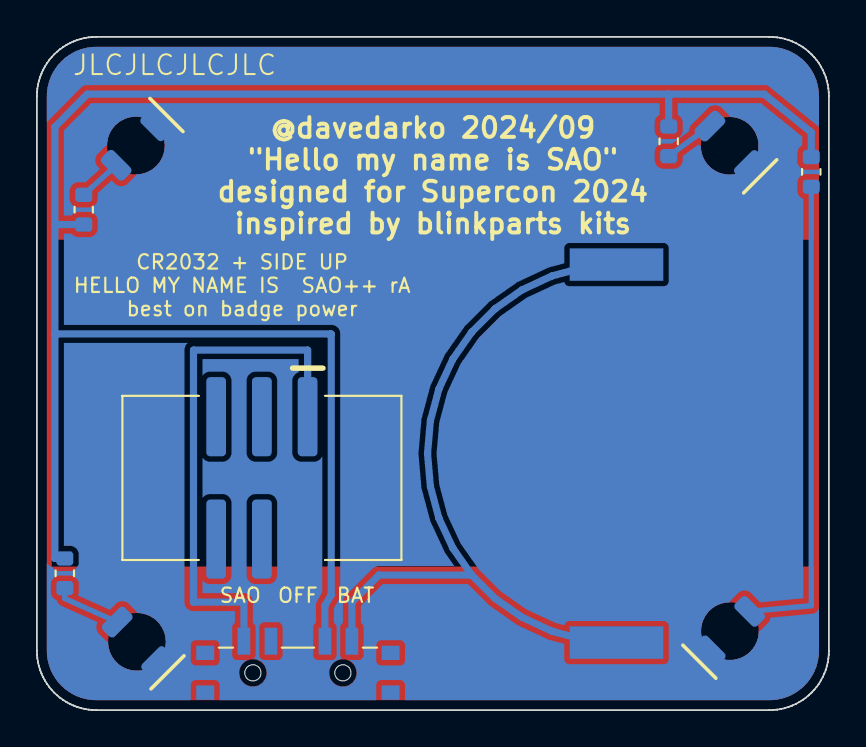
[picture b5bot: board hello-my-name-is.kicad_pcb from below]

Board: 2 copper layers, 44.0 x 37.4 mm, 11 parts (11 on the bottom side), 8 nets.
